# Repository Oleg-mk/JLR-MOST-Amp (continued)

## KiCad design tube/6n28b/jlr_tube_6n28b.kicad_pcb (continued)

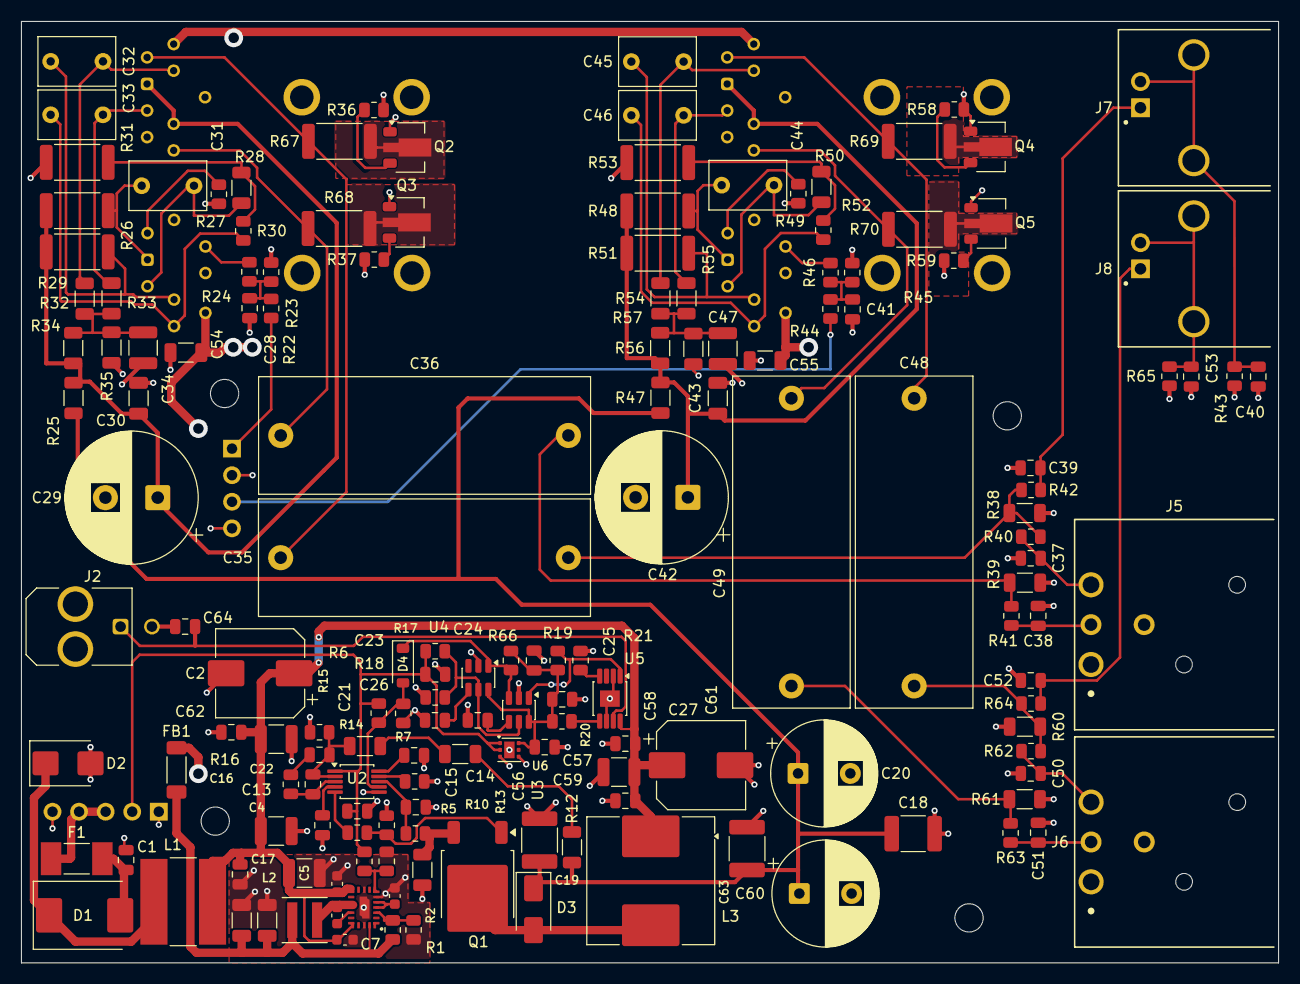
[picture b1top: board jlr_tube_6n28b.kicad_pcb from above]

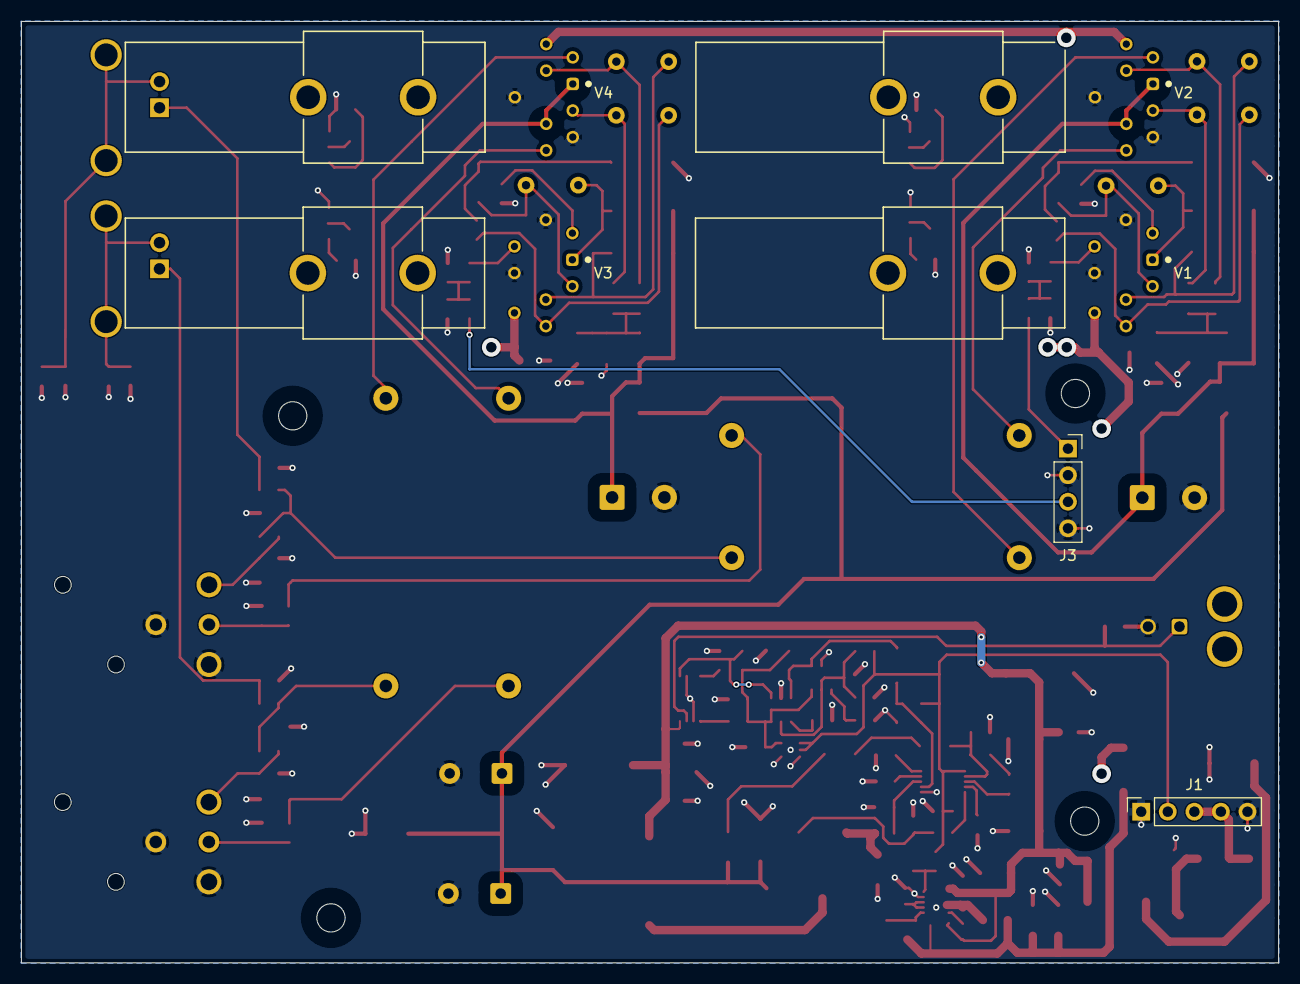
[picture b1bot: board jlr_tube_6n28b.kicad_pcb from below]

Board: 2 copper layers, 120.2 x 90.0 mm, 168 parts (6 on the bottom side), 87 nets.

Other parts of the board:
H1, H2, H3, H4: M2.5; MountingHole_2.7mm_M2.5_Standoff

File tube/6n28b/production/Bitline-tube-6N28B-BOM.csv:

Comment,Designator,Footprint,Quantity,LCSC Part #
100n 50V,"C1,C17,C27,C59,C62,C64",C_0805_2012Metric,6,
47u 50V,"C2,C61",CP_Elec_8x10,2,
10u 50V,"C4,C5,C16,C58",C_1210_3225Metric,4,
100n 50V,"C6,C7",C_0603_1608Metric,2,
100n,C8,C_0603_1608Metric,1,
1u,C9,C_0603_1608Metric,1,
22u 16V,"C10,C11,C54,C55",C_1206_3216Metric,4,
1u 50V,"C12,C23",C_0805_2012Metric,2,
1u 25V,C13,C_0805_2012Metric,1,
100n,"C14,C25,C57",C_0805_2012Metric,3,
1n,C15,C_0805_2012Metric,1,
100n 630V,"C18,C19,C63",C_1812_4532Metric,3,
10u 350V,"C20,C60",CP_Radial_D10.0mm_P5.00mm,2,
220n,C21,C_0805_2012Metric,1,
100p,C22,C_0805_2012Metric,1,
2.2u,C24,C_0805_2012Metric,1,
2.2u 10V,C26,C_0805_2012Metric,1,
100p C0G,"C28,C41",C_0805_2012Metric,2,
47u 250V,"C29,C42",CP_Radial_D12.5mm_P5.00mm,2,
100n 250V,"C30,C43",C_1206_3216Metric,2,
100n 250V,"C31,C32,C33,C44,C45,C46",C_Rect_L7.2mm_W4.5mm_P5.00mm_FKS2_FKP2_MKS2_MKP2,6,
470n 250V,"C34,C47",C_1210_3225Metric,2,
4.7u 250V MKS4,"C35,C36,C48,C49",C_Rect_L31.5mm_W11.0mm_P27.50mm_MKS4,4,
1n C0G,"C37,C38,C39,C50,C51,C52",C_0805_2012Metric,6,
10n 100V,"C40,C53",C_0805_2012Metric,2,
1.5u 10V,C56,C_0805_2012Metric,1,
SS54,D1,D_SMC,1,
SM6T30A,D2,D_SMB,1,
ES1J,D3,D_SMA,1,
BAT54W,D4,D_SOD-123,1,
3A T 0452003,F1,Fuse_Littelfuse-NANO2-451_453,1,
BLM41PG600SN1,FB1,L_1806_4516Metric,1,
гніздо 1x5,J1,PinSocket_1x05_P2.54mm_Vertical,1,
43045-0221,J2,Molex_Micro-Fit_3.0_43045-0221_2x01-1MP_P3.00mm_Horizontal,1,
гніздо 1x4,J3,PinSocket_1x04_P2.54mm_Vertical,1,
NC3MAH,"J5,J6",Neutrik_NC3MAH,2,
RCA OUT L,J7,BKL_0101153_RCA_RA,1,
RCA OUT R,J8,BKL_0101153_RCA_RA,1,
10u NRSE8040-100M,L1,L_Bourns-SRN8040_8x8.15mm,1,
2.2u CKCSA4020-2.2uH/M,L2,L_Coilcraft_XxL4030,1,
33u CDRH129RNP-330MC,L3,L_Coilcraft_MSS1278-XXX,1,
Keystone 3566,"MP1,MP2,MP3,MP4",,4,
IPD60R600P7,Q1,TO-252-2,1,
DN2540N8,"Q2,Q3,Q4,Q5",SOT-89-3,4,
100k,"R1,R3,R6,R66",R_0805_2012Metric,4,
14.3k,R2,R_0805_2012Metric,1,
18.7k,"R4,R7",R_0805_2012Metric,2,
115k,R5,R_0805_2012Metric,1,
10,"R8,R43,R65",R_0805_2012Metric,3,
47k,"R9,R16",R_0805_2012Metric,2,
0.18 1%,R10,R_1206_3216Metric,1,
100,"R11,R40,R41,R42,R62,R63,R64",R_0805_2012Metric,7,
330k,"R12,R13,R14",R_1206_3216Metric,3,
5.9k,R15,R_0805_2012Metric,1,
1M,R17,R_0805_2012Metric,1,
52.3k,R18,R_0805_2012Metric,1,
10k,"R19,R20",R_0805_2012Metric,2,
4.02k,R21,R_0805_2012Metric,1,
36k,"R22,R44",R_0805_2012Metric,2,
4.7k,"R23,R45",R_0805_2012Metric,2,
1k,"R24,R46",R_0805_2012Metric,2,
470,"R25,R47",R_1206_3216Metric,2,
27k,"R26,R48",R_2512_6332Metric,2,
820,"R27,R49",R_0805_2012Metric,2,
1M,"R28,R32,R33,R34,R35,R50,R54,R55,R56,R57",R_1206_3216Metric,10,
15k,"R29,R51",R_2512_6332Metric,2,
680,"R30,R52",R_0805_2012Metric,2,
14.3k,"R31,R53",R_2512_6332Metric,2,
620,"R36,R37,R58,R59",R_0805_2012Metric,4,
47k,"R38,R39,R60,R61",R_1206_3216Metric,4,
10k,"R67,R68,R69,R70",R_2512_6332Metric,4,
LM65625-Q1,U1,TI_RZT0020A,1,
LM5022-Q1,U2,MSOP-10_3x3mm_P0.5mm,1,
TPS7B8133DRV,U3,WSON-6-1EP_2x2mm_P0.65mm_EP1x1.6mm,1,
TPS3808G01-Q1,"U4,U6",SOT-23-6,2,
TPS1H200A-Q1,U5,HVSSOP-8-1EP_3x3mm_P0.65mm_EP1.57x1.89mm,1,
6N28B-V,"V1,V3",Valve_6N28B-V_Flat_458,2,
6N28B-V,"V2,V4",Valve_6N28B-V_Flat,2,

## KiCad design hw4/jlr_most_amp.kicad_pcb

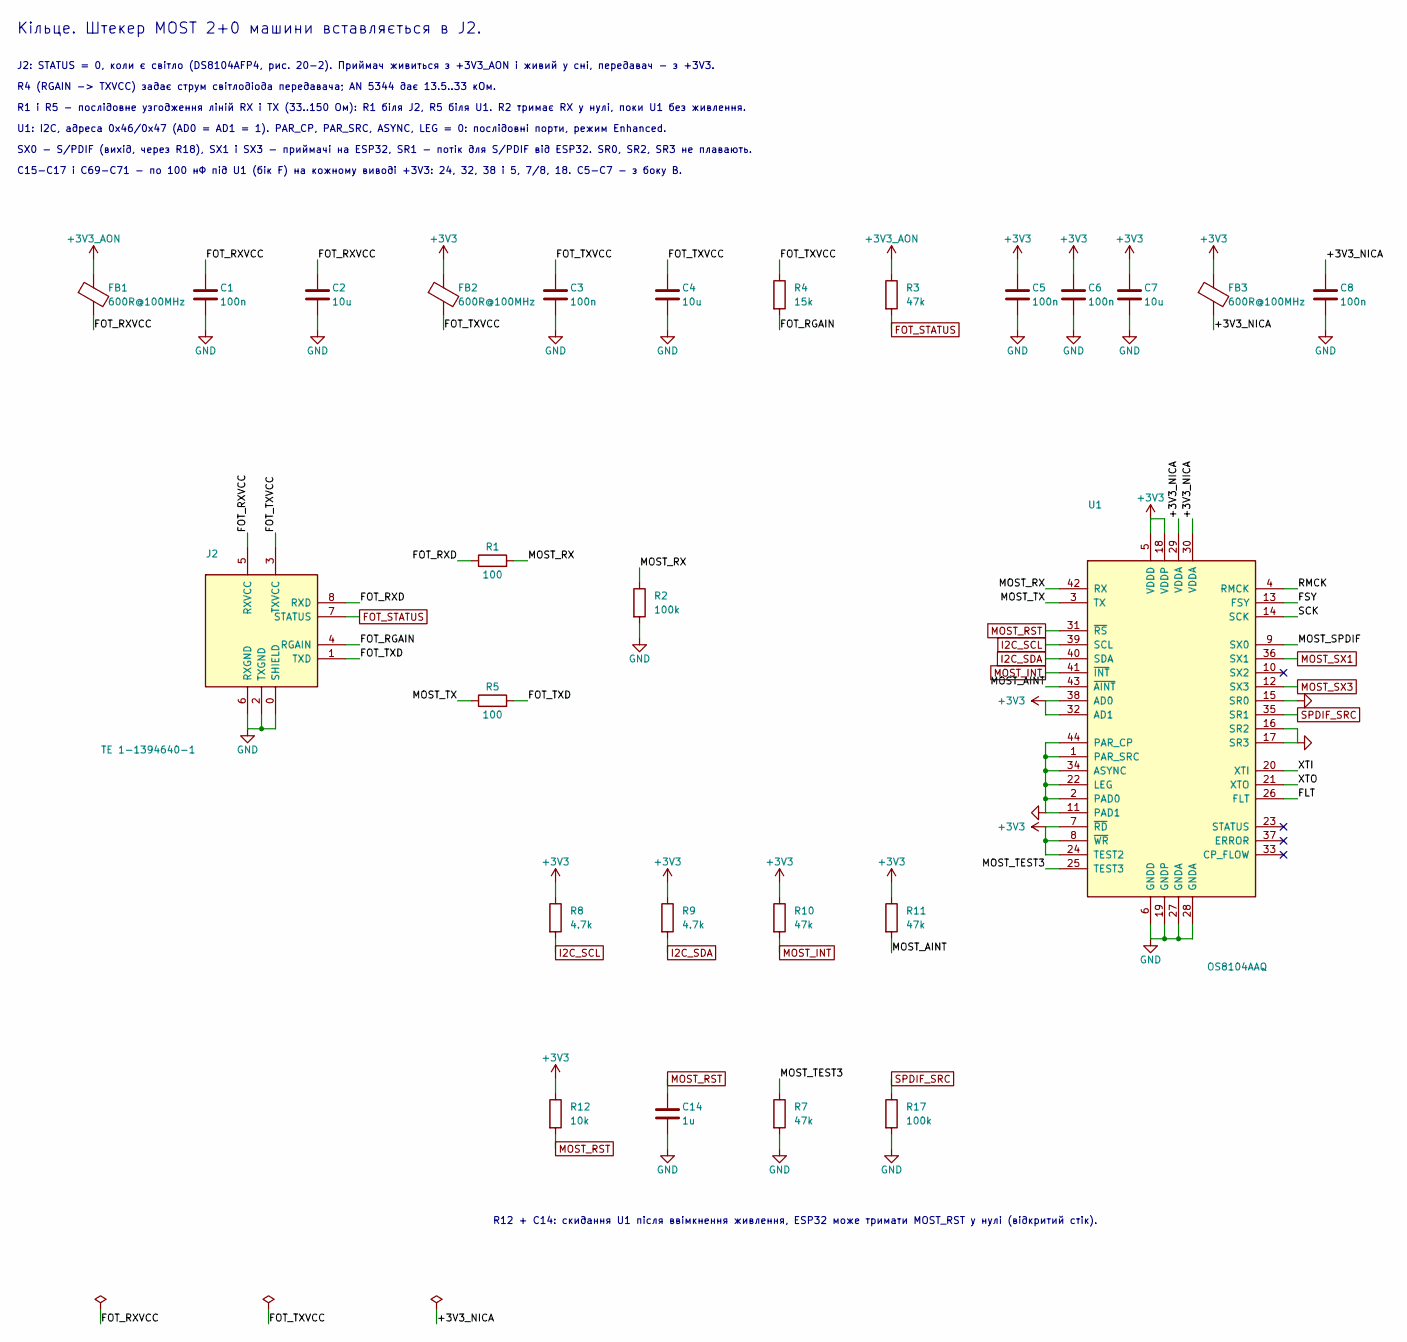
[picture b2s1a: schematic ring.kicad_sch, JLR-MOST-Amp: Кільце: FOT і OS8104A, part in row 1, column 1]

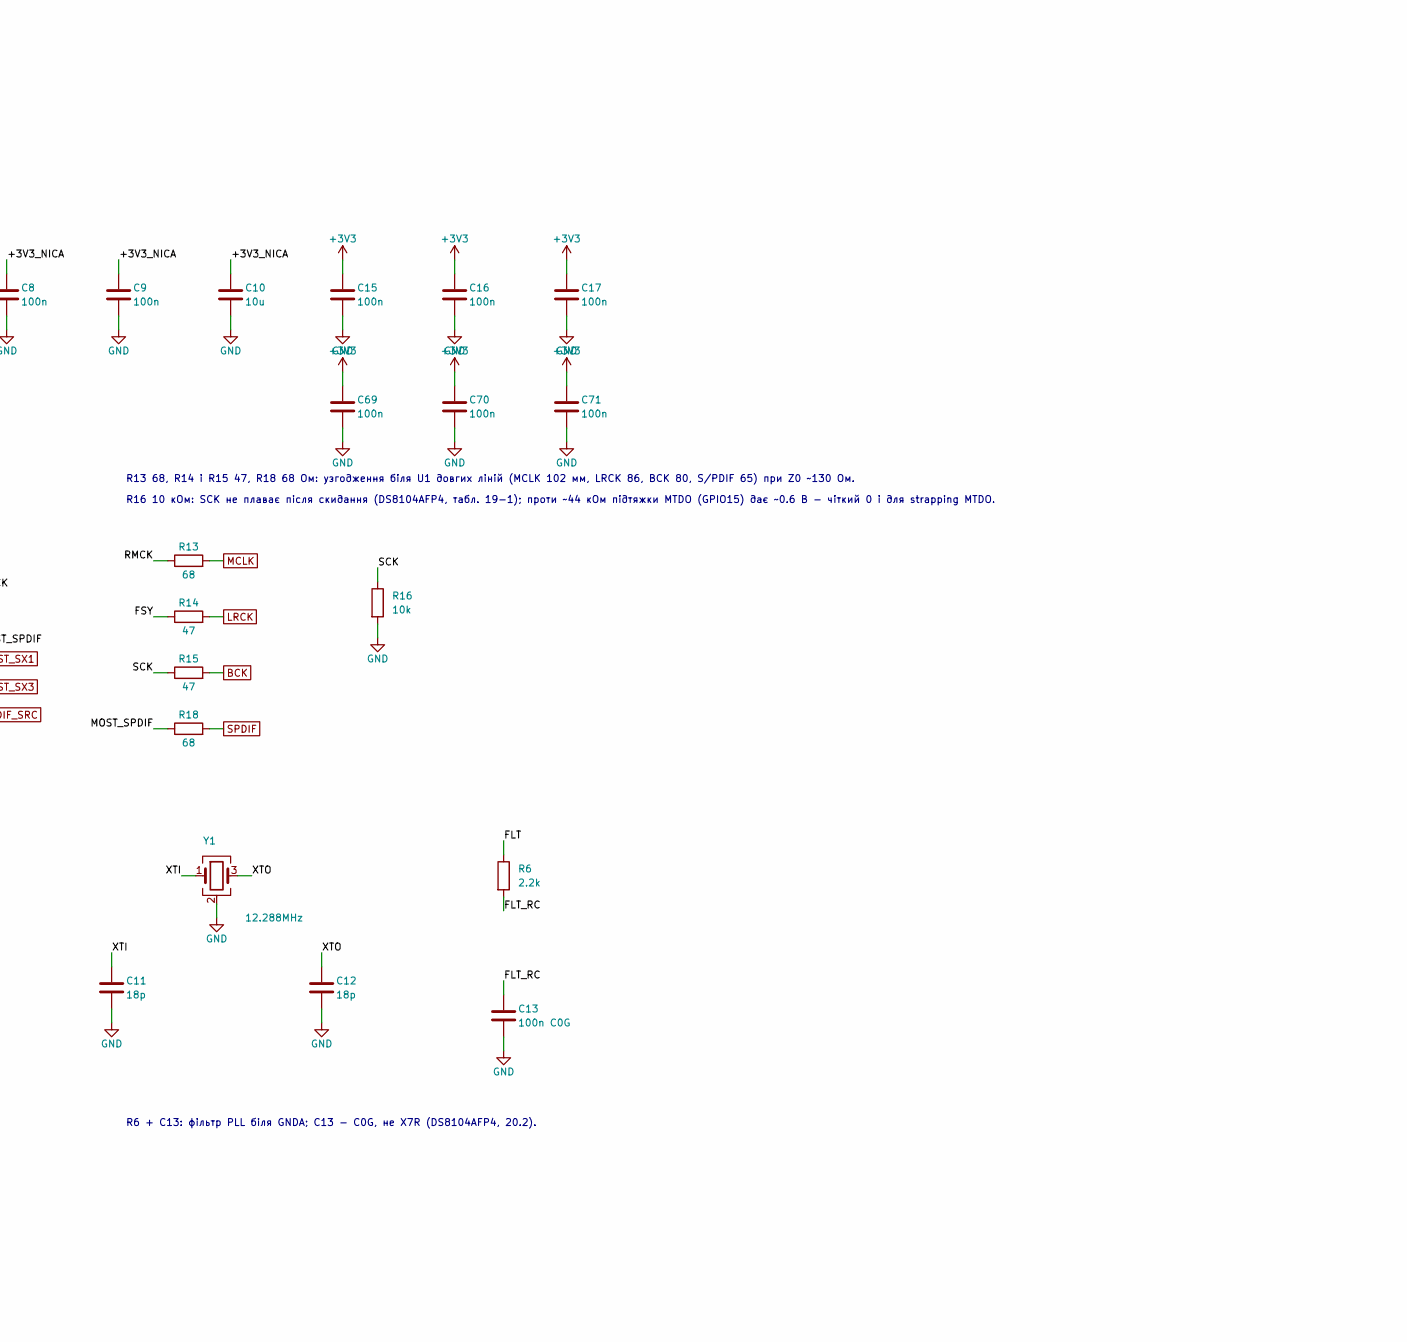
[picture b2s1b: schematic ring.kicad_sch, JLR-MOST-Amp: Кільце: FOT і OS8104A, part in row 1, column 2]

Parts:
C1, C3, C5, C6, C8, C9, C15, C16, C17, C69, C70, C71: 100n; C_0603_1608Metric
C2, C4, C7, C10: 10u; C_0805_2012Metric
C11, C12: 18p; C_0603_1608Metric
C13: 100n C0G; C_1206_3216Metric
C14: 1u; C_0603_1608Metric
FB1, FB2, FB3: 600R@100MHz; L_0603_1608Metric
J2: TE 1-1394640-1; TE_MOST_Pigtail_FOT_2+0
R1, R5: 100; R_0603_1608Metric
R2, R17: 100k; R_0603_1608Metric
R3, R7, R10, R11: 47k; R_0603_1608Metric
R4: 15k; R_0603_1608Metric
R6: 2.2k; R_0603_1608Metric
R8, R9: 4.7k; R_0603_1608Metric
R12, R16: 10k; R_0603_1608Metric
R13, R18: 68; R_0603_1608Metric
R14, R15: 47; R_0603_1608Metric
U1: OS8104AAQ; LQFP-44_10x10mm_P0.8mm
Y1: 12.288MHz; Crystal_SMD_3225-4Pin_3.2x2.5mm

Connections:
+3V3: C5.1, C6.1, C7.1, C15.1, C16.1, C17.1, C69.1, C70.1, C71.1, FB2.1, FB3.1, R8.1, R9.1, R10.1, R11.1, R12.1, U1.5 (VDDD), U1.7 (~RD), U1.8 (~WR), U1.18 (VDDP), U1.24 (TEST2), U1.32 (AD1), U1.38 (AD0); also elsewhere on the board
+3V3_AON: FB1.1, R3.1; also elsewhere on the board
/Кільце: FOT і OS8104A/+3V3_NICA: C8.1, C9.1, C10.1, FB3.2, U1.29 (VDDA), U1.30 (VDDA)
/Кільце: FOT і OS8104A/FLT: R6.1, U1.26 (FLT)
/Кільце: FOT і OS8104A/FLT_RC: C13.1, R6.2
/Кільце: FOT і OS8104A/FOT_RGAIN: J2.4 (RGAIN), R4.2
/Кільце: FOT і OS8104A/FOT_RXD: J2.8 (RXD), R1.1
/Кільце: FOT і OS8104A/FOT_RXVCC: C1.1, C2.1, FB1.2, J2.5 (RXVCC)
/Кільце: FOT і OS8104A/FOT_TXD: J2.1 (TXD), R5.2
/Кільце: FOT і OS8104A/FOT_TXVCC: C3.1, C4.1, FB2.2, J2.3 (TXVCC), R4.1
/Кільце: FOT і OS8104A/FSY: R14.1, U1.13 (FSY)
/Кільце: FOT і OS8104A/MOST_AINT: R11.2, U1.43 (~AINT)
/Кільце: FOT і OS8104A/MOST_RX: R1.2, R2.1, U1.42 (RX)
/Кільце: FOT і OS8104A/MOST_SPDIF: R18.1, U1.9 (SX0)
/Кільце: FOT і OS8104A/MOST_TEST3: R7.1, U1.25 (TEST3)
/Кільце: FOT і OS8104A/MOST_TX: R5.1, U1.3 (TX)
/Кільце: FOT і OS8104A/RMCK: R13.1, U1.4 (RMCK)
/Кільце: FOT і OS8104A/SCK: R15.1, R16.1, U1.14 (SCK)
/Кільце: FOT і OS8104A/XTI: C11.1, U1.20 (XTI), Y1.1
/Кільце: FOT і OS8104A/XTO: C12.1, U1.21 (XTO), Y1.3
BCK: R15.2; also elsewhere on the board
FOT_STATUS: J2.7 (STATUS), R3.2; also elsewhere on the board
GND: C1.2, C2.2, C3.2, C4.2, C5.2, C6.2, C7.2, C8.2, C9.2, C10.2, C11.2, C12.2, C13.2, C14.2, C15.2, C16.2, C17.2, C69.2, C70.2, C71.2, J2.0 (SHIELD), J2.2 (TXGND), J2.6 (RXGND), R2.2, R7.2, R16.2, R17.2, U1.1 (PAR_SRC), U1.2 (PAD0), U1.6 (GNDD), U1.11 (PAD1), U1.15 (SR0), U1.16 (SR2), U1.17 (SR3), U1.19 (GNDP), U1.22 (LEG), U1.27 (GNDA), U1.28 (GNDA), U1.34 (ASYNC), U1.44 (PAR_CP), Y1.2 (G), Y1.4 (G); also elsewhere on the board
I2C_SCL: R8.2, U1.39 (SCL); also elsewhere on the board
I2C_SDA: R9.2, U1.40 (SDA); also elsewhere on the board
LRCK: R14.2; also elsewhere on the board
MCLK: R13.2; also elsewhere on the board
MOST_INT: R10.2, U1.41 (~INT); also elsewhere on the board
MOST_RST: C14.1, R12.2, U1.31 (~RS); also elsewhere on the board
MOST_SX1: U1.36 (SX1); also elsewhere on the board
MOST_SX3: U1.12 (SX3); also elsewhere on the board
SPDIF: R18.2; also elsewhere on the board
SPDIF_SRC: R17.1, U1.35 (SR1); also elsewhere on the board

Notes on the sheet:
Кільце. Штекер MOST 2+0 машини вставляється в J2.
J2: STATUS = 0, коли є світло (DS8104AFP4, рис. 20-2). Приймач живиться з +3V3_AON і живий у сні, передавач - з +3V3.
R4 (RGAIN -> TXVCC) задає струм світлодіода передавача; AN 5344 дає 13.5..33 кОм.
R1 і R5 - послідовне узгодження ліній RX і TX (33..150 Ом): R1 біля J2, R5 біля U1. R2 тримає RX у нулі, поки U1 без живлення.
U1: I2C, адреса 0x46/0x47 (AD0 = AD1 = 1). PAR_CP, PAR_SRC, ASYNC, LEG = 0: послідовні порти, режим Enhanced.
SX0 - S/PDIF (вихід, через R18), SX1 і SX3 - приймачі на ESP32, SR1 - потік для S/PDIF від ESP32. SR0, SR2, SR3 не плавають.
C15-C17 і C69-C71 - по 100 нФ під U1 (бік F) на кожному виводі +3V3: 24, 32, 38 і 5, 7/8, 18. C5-C7 - з боку B.
R12 + C14: скидання U1 після ввімкнення живлення, ESP32 може тримати MOST_RST у нулі (відкритий стік).
R13 68, R14 і R15 47, R18 68 Ом: узгодження біля U1 довгих ліній (MCLK 102 мм, LRCK 86, BCK 80, S/PDIF 65) при Z0 ~130 Ом.
R16 10 кОм: SCK не плаває після скидання (DS8104AFP4, табл. 19-1); проти ~44 кОм підтяжки MTDO (GPIO15) дає ~0.6 В - чіткий 0 і для strapping MTDO.
R6 + C13: фільтр PLL біля GNDA; C13 - C0G, не X7R (DS8104AFP4, 20.2).

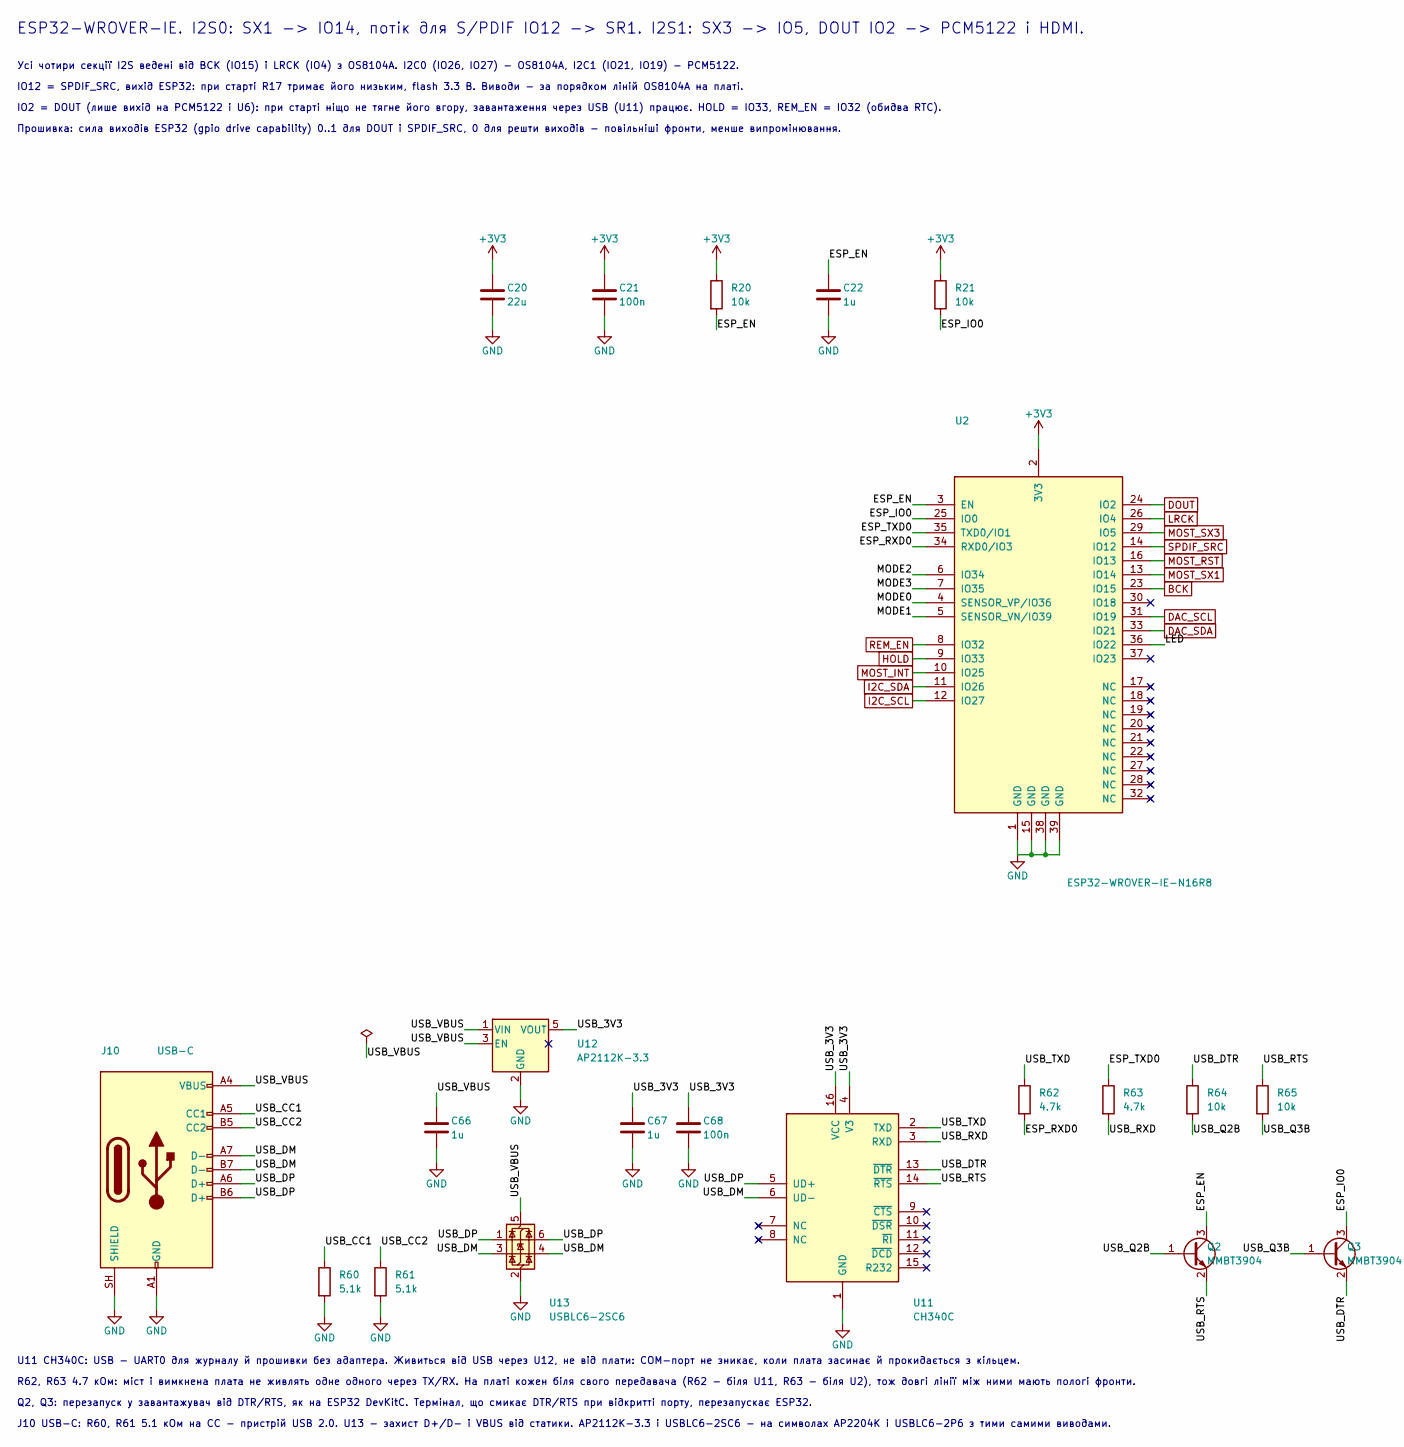
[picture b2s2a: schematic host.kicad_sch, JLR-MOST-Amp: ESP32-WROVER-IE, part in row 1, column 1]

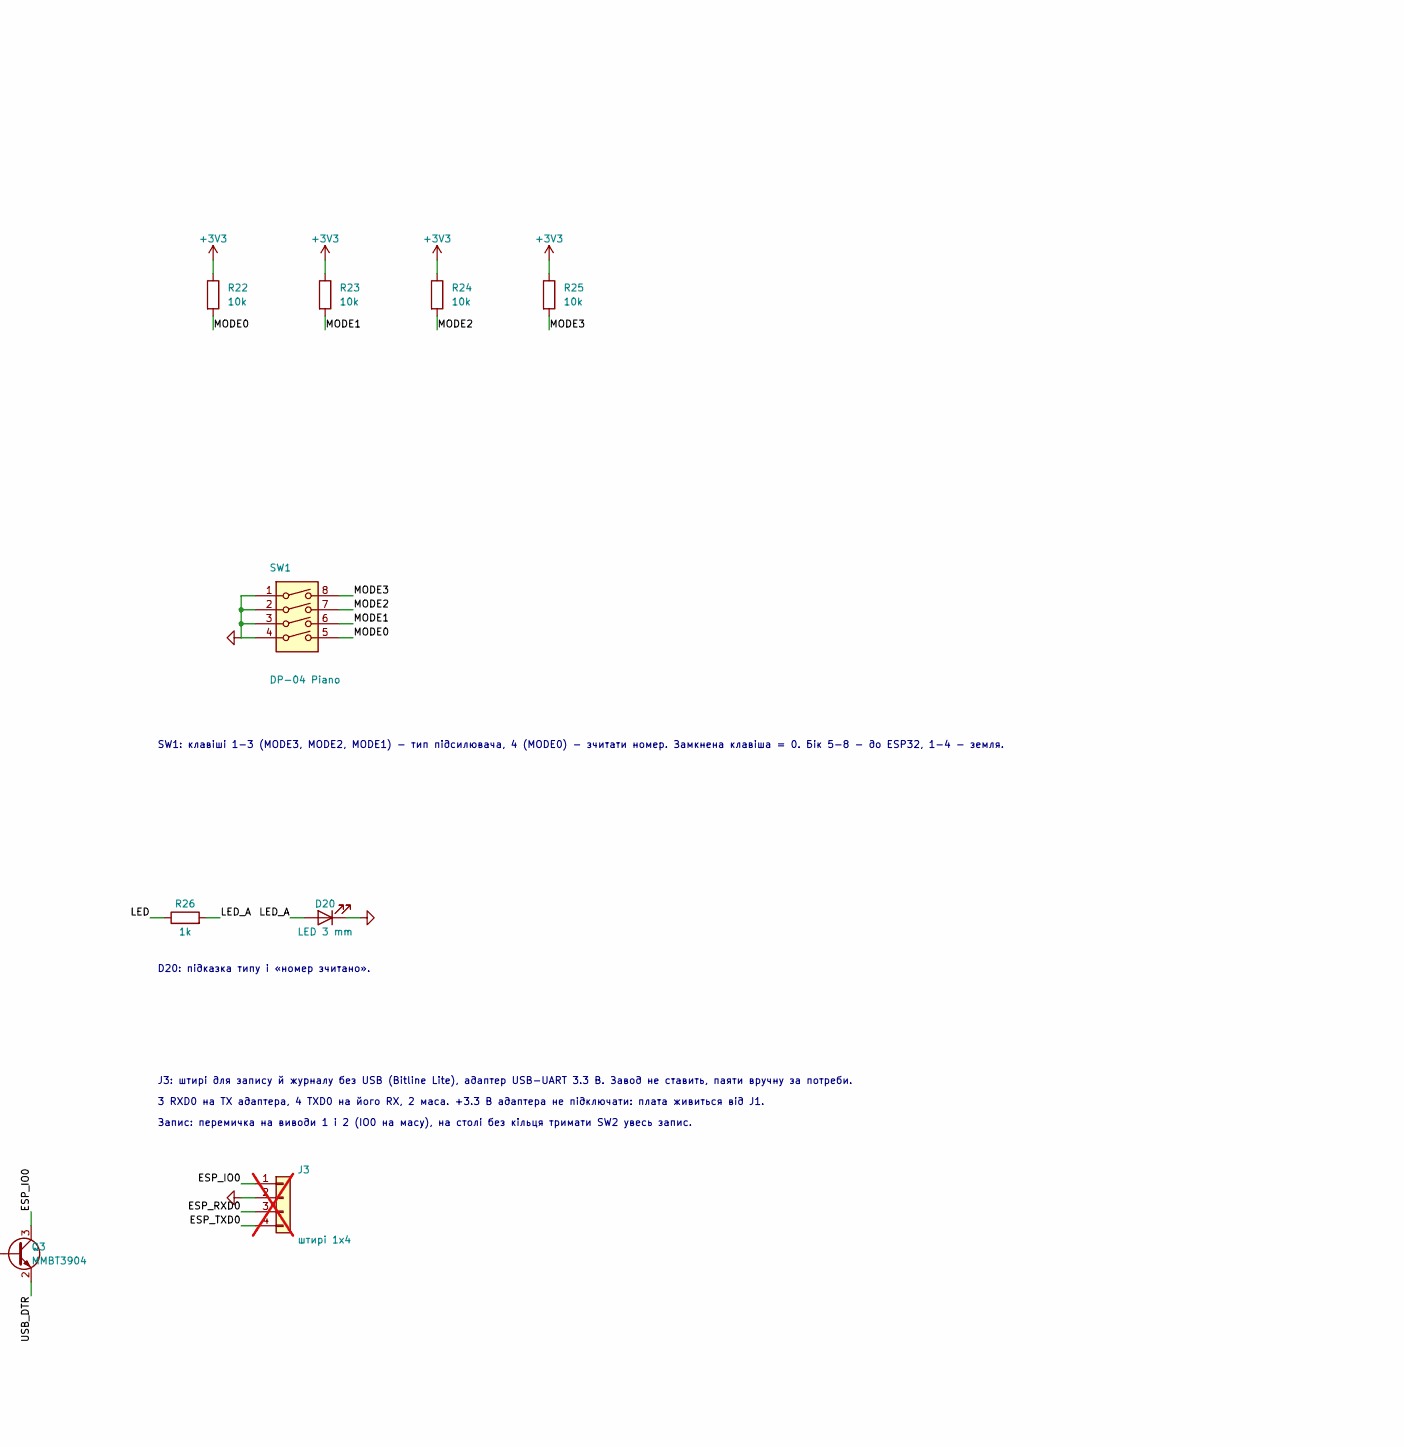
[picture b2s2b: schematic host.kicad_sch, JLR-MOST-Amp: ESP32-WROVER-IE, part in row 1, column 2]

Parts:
C20: 22u; C_1206_3216Metric
C21, C68: 100n; C_0603_1608Metric
C22, C66, C67: 1u; C_0603_1608Metric
D20: LED 3 mm; LED_D3.0mm
J3: штирі 1x4; PinHeader_1x04_P2.54mm_Vertical; not fitted
J10: USB-C; USB_C_Receptacle_14P_SideInsert_THT
Q2, Q3: MMBT3904; SOT-23
R20, R21, R22, R23, R24, R25, R64, R65: 10k; R_0603_1608Metric
R26: 1k; R_0603_1608Metric
R60, R61: 5.1k; R_0603_1608Metric
R62, R63: 4.7k; R_0603_1608Metric
SW1: DP-04 Piano; SW_DIP_SPSTx04_Piano_10.8x11.72mm_W7.62mm_P2.54mm
U2: ESP32-WROVER-IE-N16R8; ESP32-WROVER-IE
U11: CH340C; SOIC-16_3.9x9.9mm_P1.27mm
U12: AP2112K-3.3; SOT-23-5
U13: USBLC6-2SC6; SOT-23-6

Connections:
+3V3: C20.1, C21.1, R20.1, R21.1, R22.1, R23.1, R24.1, R25.1, U2.2 (3V3); also elsewhere on the board
/ESP32-WROVER-IE/ESP_EN: C22.1, Q2.3 (C), R20.2, U2.3 (EN)
/ESP32-WROVER-IE/ESP_IO0: J3.1, Q3.3 (C), R21.2, U2.25 (IO0)
/ESP32-WROVER-IE/ESP_RXD0: J3.3, R62.2, U2.34 (RXD0/IO3)
/ESP32-WROVER-IE/ESP_TXD0: J3.4, R63.1, U2.35 (TXD0/IO1)
/ESP32-WROVER-IE/LED: R26.1, U2.36 (IO22)
/ESP32-WROVER-IE/LED_A: D20.2 (A), R26.2
/ESP32-WROVER-IE/MODE0: R22.2, SW1.5, U2.4 (SENSOR_VP/IO36)
/ESP32-WROVER-IE/MODE1: R23.2, SW1.6, U2.5 (SENSOR_VN/IO39)
/ESP32-WROVER-IE/MODE2: R24.2, SW1.7, U2.6 (IO34)
/ESP32-WROVER-IE/MODE3: R25.2, SW1.8, U2.7 (IO35)
/ESP32-WROVER-IE/USB_3V3: C67.1, C68.1, U11.4 (V3), U11.16 (VCC), U12.5 (VOUT)
/ESP32-WROVER-IE/USB_CC1: J10.A5 (CC1), R60.1
/ESP32-WROVER-IE/USB_CC2: J10.B5 (CC2), R61.1
/ESP32-WROVER-IE/USB_DM: J10.A7 (D-), J10.B7 (D-), U11.6 (UD-), U13.3 (I/O2), U13.4 (I/O2)
/ESP32-WROVER-IE/USB_DP: J10.A6 (D+), J10.B6 (D+), U11.5 (UD+), U13.1 (I/O1), U13.6 (I/O1)
/ESP32-WROVER-IE/USB_DTR: Q3.2 (E), R64.1, U11.13 (~DTR)
/ESP32-WROVER-IE/USB_Q2B: Q2.1 (B), R64.2
/ESP32-WROVER-IE/USB_Q3B: Q3.1 (B), R65.2
/ESP32-WROVER-IE/USB_RTS: Q2.2 (E), R65.1, U11.14 (~RTS)
/ESP32-WROVER-IE/USB_RXD: R63.2, U11.3 (RXD)
/ESP32-WROVER-IE/USB_TXD: R62.1, U11.2 (TXD)
/ESP32-WROVER-IE/USB_VBUS: C66.1, J10.A4 (VBUS), J10.A9 (VBUS), J10.B4 (VBUS), J10.B9 (VBUS), U12.1 (VIN), U12.3 (EN), U13.5 (VBUS)
BCK: U2.23 (IO15); also elsewhere on the board
DAC_SCL: U2.31 (IO19); also elsewhere on the board
DAC_SDA: U2.33 (IO21); also elsewhere on the board
DOUT: U2.24 (IO2); also elsewhere on the board
GND: C20.2, C21.2, C22.2, C66.2, C67.2, C68.2, D20.1 (K), J3.2, J10.A1 (GND), J10.A12 (GND), J10.B1 (GND), J10.B12 (GND), J10.SH (SHIELD), R60.2, R61.2, SW1.1, SW1.2, SW1.3, SW1.4, U2.1 (GND), U2.15 (GND), U2.38 (GND), U2.39 (GND), U11.1 (GND), U12.2 (GND), U13.2 (GND); also elsewhere on the board
HOLD: U2.9 (IO33); also elsewhere on the board
I2C_SCL: U2.12 (IO27); also elsewhere on the board
I2C_SDA: U2.11 (IO26); also elsewhere on the board
LRCK: U2.26 (IO4); also elsewhere on the board
MOST_INT: U2.10 (IO25); also elsewhere on the board
MOST_RST: U2.16 (IO13); also elsewhere on the board
MOST_SX1: U2.13 (IO14); also elsewhere on the board
MOST_SX3: U2.29 (IO5); also elsewhere on the board
REM_EN: U2.8 (IO32); also elsewhere on the board
SPDIF_SRC: U2.14 (IO12); also elsewhere on the board

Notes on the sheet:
ESP32-WROVER-IE. I2S0: SX1 -> IO14, потік для S/PDIF IO12 -> SR1. I2S1: SX3 -> IO5, DOUT IO2 -> PCM5122 і HDMI.
Усі чотири секції I2S ведені від BCK (IO15) і LRCK (IO4) з OS8104A. I2C0 (IO26, IO27) - OS8104A, I2C1 (IO21, IO19) - PCM5122.
IO12 = SPDIF_SRC, вихід ESP32: при старті R17 тримає його низьким, flash 3.3 В. Виводи - за порядком ліній OS8104A на платі.
IO2 = DOUT (лише вихід на PCM5122 і U6): при старті ніщо не тягне його вгору, завантаження через USB (U11) працює. HOLD = IO33, REM_EN = IO32 (обидва RTC).
Прошивка: сила виходів ESP32 (gpio drive capability) 0..1 для DOUT і SPDIF_SRC, 0 для решти виходів - повільніші фронти, менше випромінювання.
SW1: клавіші 1-3 (MODE3, MODE2, MODE1) - тип підсилювача, 4 (MODE0) - зчитати номер. Замкнена клавіша = 0. Бік 5-8 - до ESP32, 1-4 - земля.
D20: підказка типу і «номер зчитано».
J3: штирі для запису й журналу без USB (Bitline Lite), адаптер USB-UART 3.3 В. Завод не ставить, паяти вручну за потреби.
3 RXD0 на TX адаптера, 4 TXD0 на його RX, 2 маса. +3.3 В адаптера не підключати: плата живиться від J1.
Запис: перемичка на виводи 1 і 2 (IO0 на масу), на столі без кільця тримати SW2 увесь запис.
U11 CH340C: USB - UART0 для журналу й прошивки без адаптера. Живиться від USB через U12, не від плати: COM-порт не зникає, коли плата засинає й прокидається з кільцем.
R62, R63 4.7 кОм: міст і вимкнена плата не живлять одне одного через TX/RX. На платі кожен біля свого передавача (R62 - біля U11, R63 - біля U2), тож довгі лінії між ними мають пологі фронти.
Q2, Q3: перезапуск у завантажувач від DTR/RTS, як на ESP32 DevKitC. Термінал, що смикає DTR/RTS при відкритті порту, перезапускає ESP32.
J10 USB-C: R60, R61 5.1 кОм на CC - пристрій USB 2.0. U13 - захист D+/D- і VBUS від статики. AP2112K-3.3 і USBLC6-2SC6 - на символах AP2204K і USBLC6-2P6 з тими самими виводами.
